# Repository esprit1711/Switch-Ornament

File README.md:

# Switch-Ornament
tinyest possible Gif Player that looks like a Nintendo Switch
IN CASE YOU WANT TO BUILD YOUR OWN SWITCH ORNAMENT, PLEASE CONTACT ME. I WANT TO FIX SOME TINY PROBLEMS WITH THE BOARD IN VERSION 1.4 :)

Here, you will find everything to Copy my GIF Player, that looks like a Nintendo Switch. This Project use a 0.96" 80x160 Pixel TFT with st7735 Driver.
The Source Code is based on the "ESP32-LGFX-SDCard-GifPlayer" Example of the "AnimatedGIF" library from "bitbank2".
The Inspiration for this Project is the Nintendo Switch Ornamend from scottbez1 (you can find his Video in der Credits). He use a slightly bigger Screen, with much higher Resolution but i want the smalest possible Switch.

Part of this Project is a DIY Powerbank only for this device so you can use it as a christmas ornament. Powerbank and Switch are connected over a 65cm long cable with 0.04mm² wires. to achive also the tinyest possible powerbank, i crated a custom Board with Li-Po Charger and Power Switch (you can charge the battery and can still use the device). To use the powerbank also as base, i put 3 magnets inside the switch case and powerbank so it will hold very well together without any bad looking mechanic

The Mainboard is optimised to be ordered at jlcpcb and use the assembly Service. You will find everything jlcpcb need (gerber, BOM and positions file) in the "production" Folder of the KiCad Project. You want to choose a 1.6mm board thickness, the Option "Specify a location" at "Remove Order Number" and check the orientation of every part after upload and check the BOM. You also need to order the tiny Buttons and the TFT so you can assemble it after you got the Boards.

Buttons:

https://de.aliexpress.com/item/1005003752959323.html

0.96" TFT (WELDET TYPE!):

https://de.aliexpress.com/item/1005003806330978.html

After everything is assembled, you need to prepare a USB Cable so the connection will match with the silkscreen. You can solder it directly on the Pads, or use a 1.27mm pinheader. Solder the "BOOT" bridge at the front of the board, connect the USB cable to your PC, open the Firmware with Arduino IDE and upload the Code.
To upload the code, you need to copy the library folder in your local Arduino library folder and install the ESP32 via Board Manager. after you prepared this, you just need to choose the right board (ESP32C3 Dev Module) and Port and set every setting like on the following picture:

After a successful upload, disconnect the USB cable and remove the "BOOT" solder bridge. Now, you dont need to solder the Bridge anymore to upload a Code via USB. You can also disconnect the USB Cable (or leave it, if you want to use it as the power source) and power the device via the +5V and GND Pads. The Software is prepared to update the firmware, if a "SO_update.bin" was found on the SD-Card, so in case of an Update, you dont need the USB connection anymore.

The Case for the powerbank is printed with an FDM 3D Printer. You need 3x M2 Threaded inserts and M2x6mm screws to assemble everything. As a battery, i use 402535 320mAh LiPo. A piece of double sieded tape between the battery and board is recommended.

The magnets i use are 2mm x 1mm (diameter x thickness). Use a pen to mark the polarity, so you know everytime the orientation.

The Case for the Nintendo Switch is printed with an Resin Printer. I had to do some tests to find the perfect dimensions, but now everything should fit very well.
Paint can bring some thickness, so be carefull with to mouch Paint.

Hardware:

Changelog:
1.1:
- Support for alternative ST7735 Displays (if Color ist wrong, try GPIO09 connect to VCC (alternative Display Type))

1.2:
- Check for GIF Header. Ignor file if Header ist not "GIF"
- alternative library (chose before compile code)

1.3:
- PNG support
- Left Button trigger play previous file instead of changing the Brightness of the Screen

1.4:
- Clean Code, so it should be now better to maintain
- Fix a problem when use the LGFX library (use a variable from eSPI to initialise the SD Card (old testing stuff))
- improve Version Information and SD Card Info Screen. Its now cleaner and stay for 2 instead of 1 second
- change brightness level by push and hold left (reduce) or right (increase) button for more than 1 second
- speed up initialisation slightly

Credits:

https://github.com/bitbank2/AnimatedGIF

https://github.com/Bodmer/TFT_eSPI

https://www.youtube.com/watch?v=zJxyTgLjIB8

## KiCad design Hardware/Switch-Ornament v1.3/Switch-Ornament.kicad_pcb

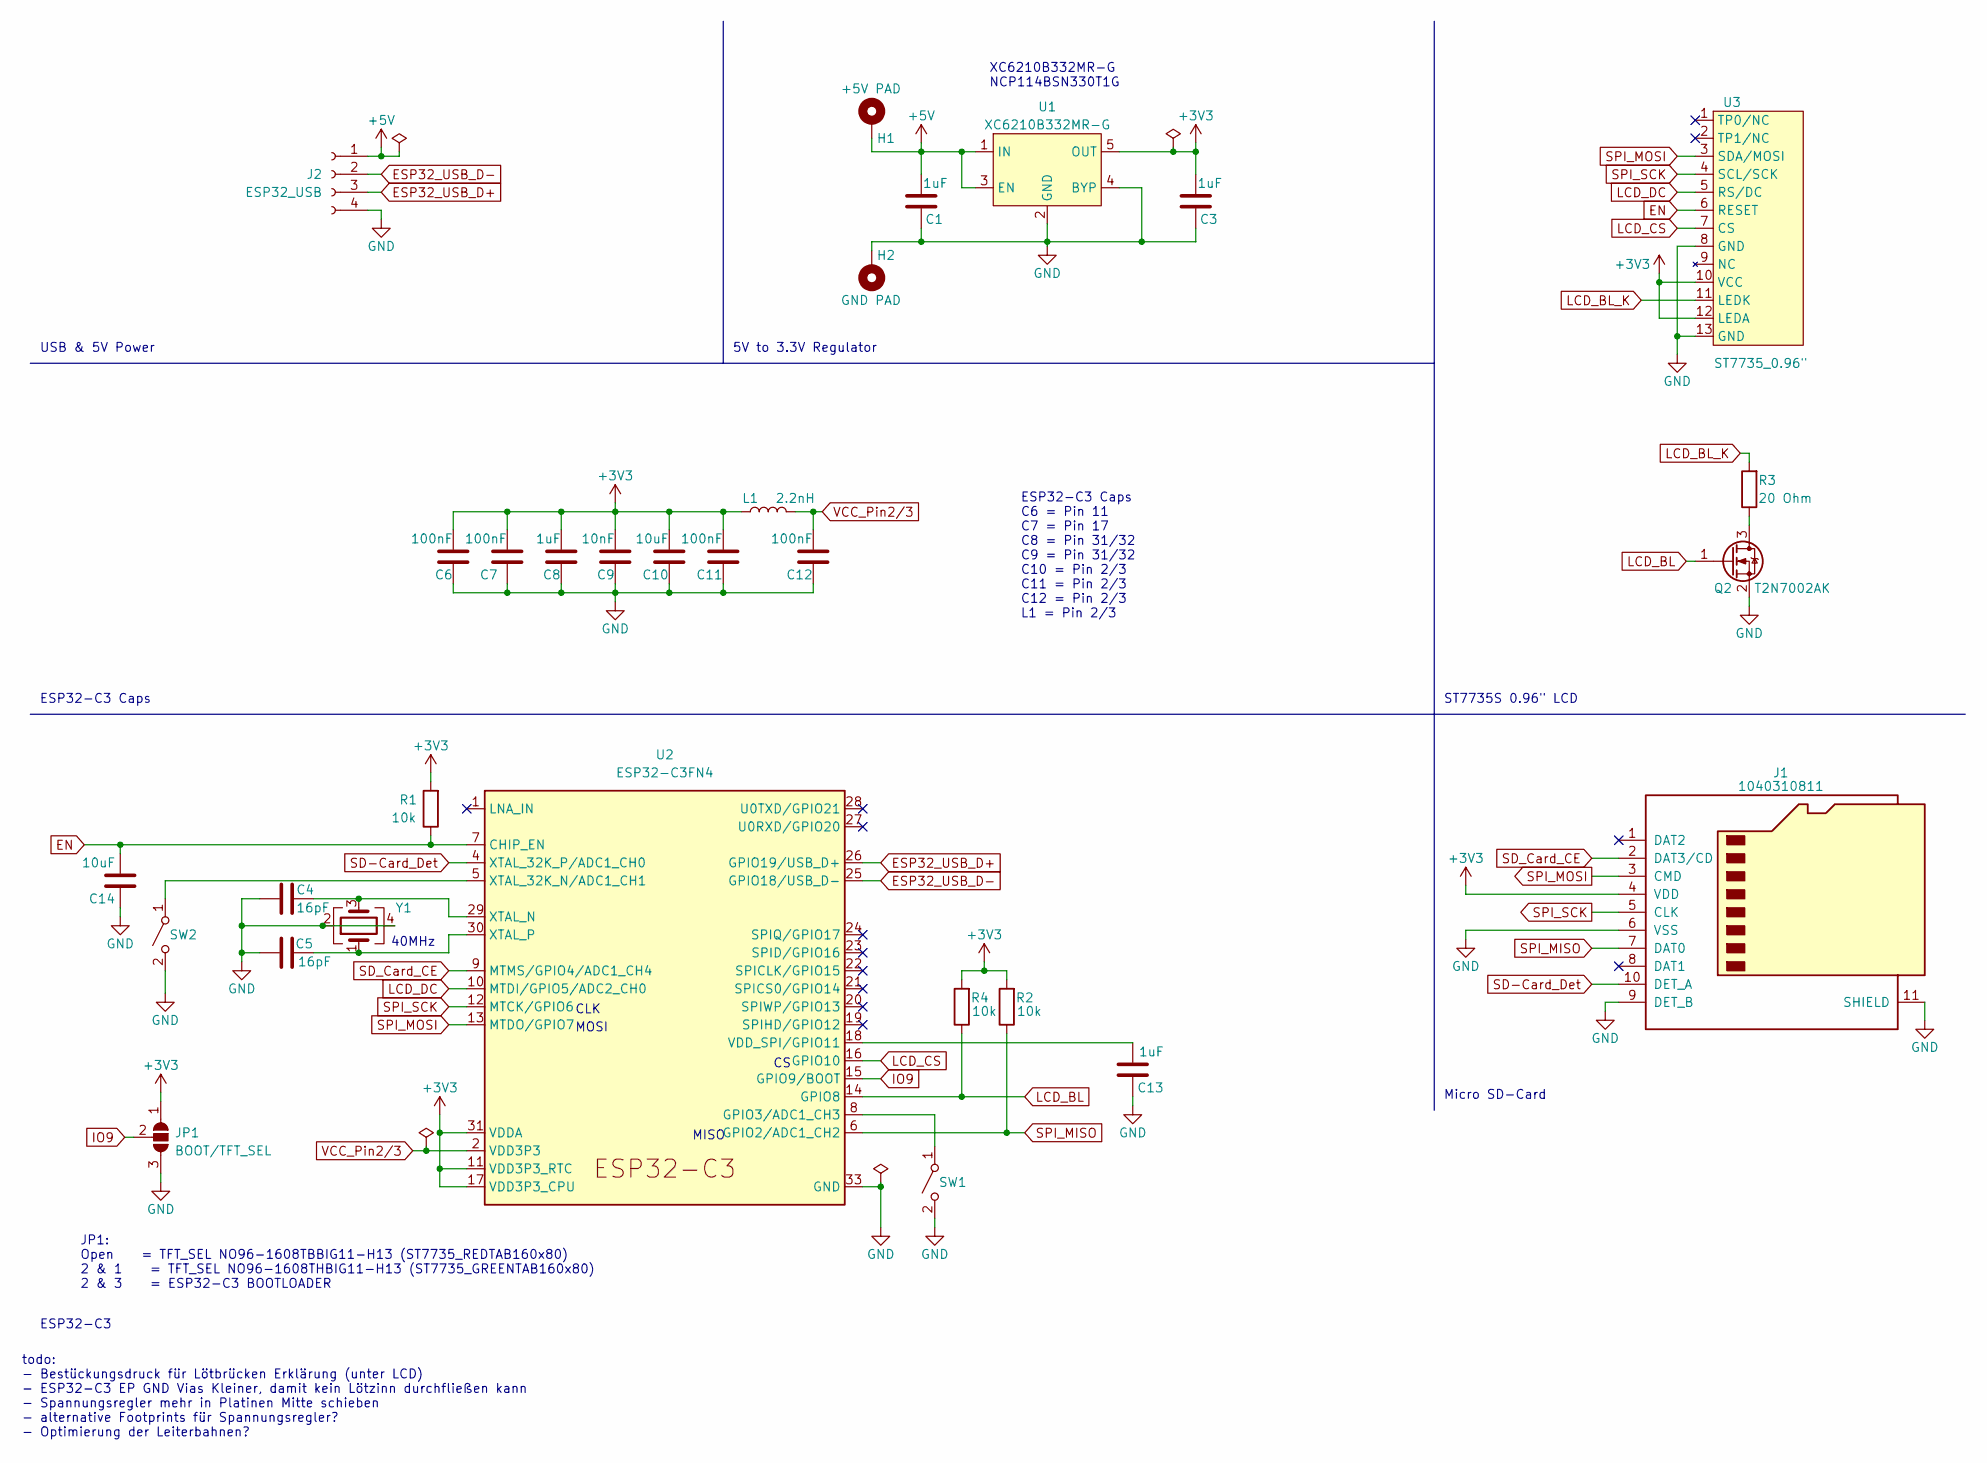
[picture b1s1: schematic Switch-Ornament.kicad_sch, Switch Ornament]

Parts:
C1, C3, C8, C13: 1uF; C_0603_1608Metric
C4, C5: 16pF; C_0603_1608Metric
C6, C7, C11, C12: 100nF; C_0603_1608Metric
C9: 10nF; C_0603_1608Metric
C10, C14: 10uF; C_0603_1608Metric
H1: +5V PAD; TestPoint_Pad_D1.5mm
H2: GND PAD; TestPoint_Pad_D1.5mm
J1: 1040310811; microSD_HC_Molex_104031-0811
J2: ESP32_USB; PinHeader_1x04_P1.27mm_Vertical
JP1: BOOT/TFT_SEL; SolderJumper-3_P2.0mm_Open_TrianglePad1.0x1.5mm_NumberLabels
L1: 2.2nH; L_0603_1608Metric
Q2: T2N7002AK; SOT-23
R1, R2, R4: 10k; R_0603_1608Metric
R3: 20 Ohm; R_0603_1608Metric
SW1, SW2: EVP-BB2A9B000; EVPBB
U1: XC6210B332MR-G; TSOP-5_1.65x3.05mm_P0.95mm
U2: ESP32-C3FN4; QFN-32-1EP_5x5mm_P0.5mm_EP3.45x3.45mm
U3: ST7735_0.96"; ST7735S 0.96
Y1: 7B040000H01; Crystal_SMD_3225-4Pin_3.2x2.5mm

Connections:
+3V3: C3.2, C6.2, C7.2, C8.2, C9.2, C10.2, C11.2, J1.4 (VDD), JP1.1 (A), L1.1, R1.2, R2.2, R4.2, U1.5 (OUT), U2.11 (VDD3P3_RTC), U2.17 (VDD3P3_CPU), U2.31 (VDDA), U2.32 (VDDA), U3.10 (VCC), U3.12 (LEDA)
+5V: C1.2, H1.1, J2.1, U1.1 (IN), U1.3 (EN)
EN: C14.2, R1.1, U2.7 (CHIP_EN), U3.6 (RESET)
ESP32_USB_D+: J2.3, U2.26 (GPIO19/USB_D+)
ESP32_USB_D-: J2.2, U2.25 (GPIO18/USB_D-)
GND: C1.1, C3.1, C4.2, C5.1, C6.1, C7.1, C8.1, C9.1, C10.1, C11.1, C12.1, C13.1, C14.1, H2.1, J1.6 (VSS), J1.9 (DET_B), J1.11 (SHIELD), J2.4, JP1.3 (B), Q2.2 (S), SW1.2 (B), SW2.2 (B), U1.2 (GND), U1.4 (BYP), U2.33 (GND), U3.8 (GND), U3.13 (GND), Y1.2, Y1.4
IO9: JP1.2 (C), U2.15 (GPIO9/BOOT)
LCD_BL: Q2.1 (G), R4.1, U2.14 (GPIO8)
LCD_BL_K: R3.2, U3.11 (LEDK)
LCD_CS: U2.16 (GPIO10), U3.7 (CS)
LCD_DC: U2.10 (MTDI/GPIO5/ADC2_CH0), U3.5 (RS/DC)
unnamed: Q2.3 (D), R3.1
unnamed: SW1.1 (A), U2.8 (GPIO3/ADC1_CH3)
unnamed: SW2.1 (A), U2.5 (XTAL_32K_N/ADC1_CH1)
unnamed: C13.2, U2.18 (VDD_SPI/GPIO11)
unnamed: C4.1, U2.29 (XTAL_N), Y1.3
unnamed: C5.2, U2.30 (XTAL_P), Y1.1
SD-Card_Det: J1.10 (DET_A), U2.4 (XTAL_32K_P/ADC1_CH0)
SD_Card_CE: J1.2 (DAT3/CD), U2.9 (MTMS/GPIO4/ADC1_CH4)
SPI_MISO: J1.7 (DAT0), R2.1, U2.6 (GPIO2/ADC1_CH2)
SPI_MOSI: J1.3 (CMD), U2.13 (MTDO/GPIO7), U3.3 (SDA/MOSI)
SPI_SCK: J1.5 (CLK), U2.12 (MTCK/GPIO6), U3.4 (SCL/SCK)
VCC_Pin2/3: C12.2, L1.2, U2.2 (VDD3P3), U2.3 (VDD3P3)

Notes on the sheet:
ST7735S 0.96" LCD
CLK
40MHz
USB & 5V Power
XC6210B332MR-G NCP114BSN330T1G
ESP32-C3 Caps
MOSI
Micro SD-Card
todo: - Bestückungsdruck für Lötbrücken Erklärung (unter LCD) - ESP32-C3 EP GND Vias Kleiner, damit kein Lötzinn durchfließen kann - Spannungsregler mehr in Platinen Mitte schieben - alternative Footprints für Spannungsregler? - Optimierung der Leiterbahnen?
ESP32-C3 Caps C6 = Pin 11 C7 = Pin 17 C8 = Pin 31/32 C9 = Pin 31/32 C10 = Pin 2/3 C11 = Pin 2/3 C12 = Pin 2/3 L1 = Pin 2/3
MISO
ESP32-C3
JP1: Open = TFT_SEL NO96-1608TBBIG11-H13 (ST7735_REDTAB160x80) 2 & 1 = TFT_SEL NO96-1608THBIG11-H13 (ST7735_GREENTAB160x80) 2 & 3 = ESP32-C3 BOOTLOADER
5V to 3.3V Regulator

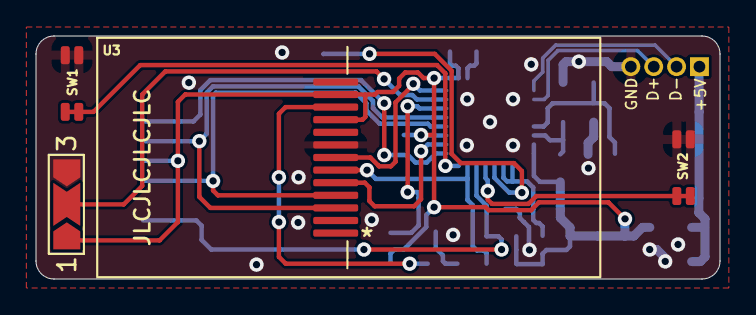
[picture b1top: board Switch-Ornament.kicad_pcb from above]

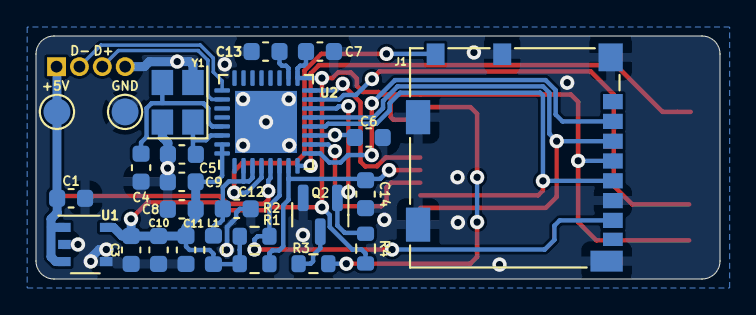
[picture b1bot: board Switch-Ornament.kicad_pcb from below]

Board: 2 copper layers, 38.0 x 13.5 mm, 30 parts (26 on the bottom side), 23 nets.

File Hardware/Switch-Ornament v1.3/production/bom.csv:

Designator,Footprint,Quantity,Value,LCSC Part #
"C1, C13, C3, C8",0603,4,1uF,
"C10, C14",0603,2,10uF,
"C11, C12, C6, C7",0603,4,100nF,
"C4, C5",0603,2,16pF,
C9,0603,1,10nF,
H1,TestPoint_Pad_D1.5mm,1,+5V PAD,
H2,TestPoint_Pad_D1.5mm,1,GND PAD,
J1,microSD_HC_Molex_104031-0811,1,1040310811,
J2,PinHeader_1x04_P1.27mm_Vertical,1,ESP32_USB,
JP1,SolderJumper-2_P1.3mm_Open_TrianglePad1.0x1.5mm,1,BOOT,
L1,0603,1,2.2nH,
Q2,SOT-23,1,T2N7002AK,
"R1, R2, R4",0603,3,10k,
R3,0603,1,20 Ohm,
"SW1, SW2",EVPBB,2,EVP-BB2A9B000,
U1,TSOP-5_1.65x3.05mm_P0.95mm,1,XC6210B332MR-G,
U2,QFN-32-1EP_5x5mm_P0.5mm_EP3.45x3.45mm,1,ESP32-C3FN4,
U3,ST7735S 0.96,1,"ST7735_0.96""",
Y1,Crystal_SMD_3225-4Pin_3.2x2.5mm,1,7B040000H01,

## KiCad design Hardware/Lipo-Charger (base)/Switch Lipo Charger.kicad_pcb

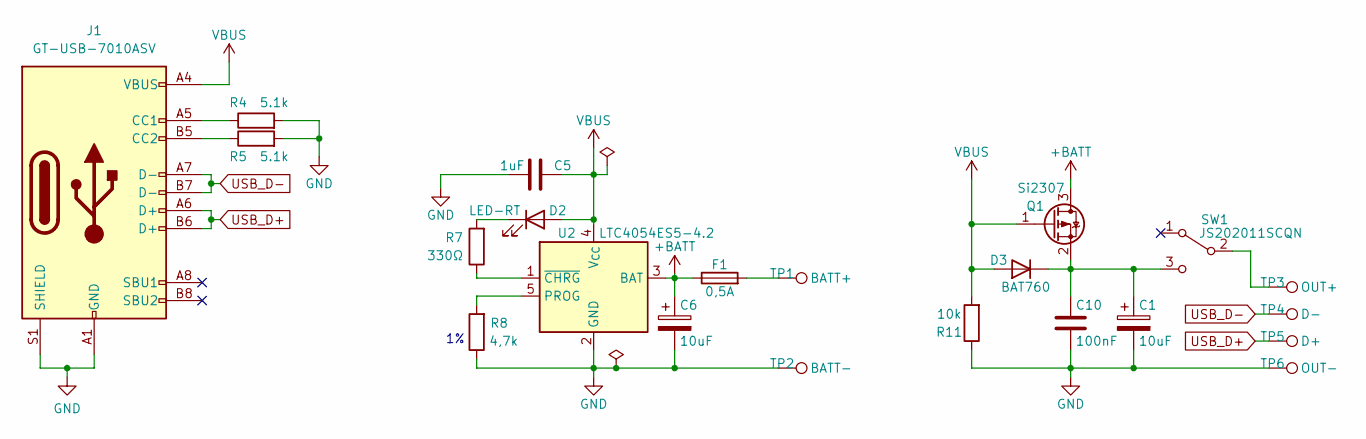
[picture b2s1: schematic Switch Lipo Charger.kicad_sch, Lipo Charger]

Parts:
C1, C6: 10uF; CP_EIA-2012-15_AVX-P_Pad1.30x1.05mm_HandSolder
C5: 1uF; C_0805_2012Metric_Pad1.18x1.45mm_HandSolder
C10: 100nF; C_0603_1608Metric_Pad1.08x0.95mm_HandSolder
D2: LED-RT; LED_0805_2012Metric_Pad1.15x1.40mm_HandSolder
D3: BAT760; D_SOD-123F
F1: 0,5A; Fuse_1206_3216Metric_Pad1.42x1.75mm_HandSolder
J1: GT-USB-7010ASV; USB_C_Receptacle_G-Switch_GT-USB-7010ASV
Q1: Si2307; SOT-23
R4, R5: 5.1k; R_0603_1608Metric_Pad0.98x0.95mm_HandSolder
R7: 330Ω; R_0603_1608Metric_Pad0.98x0.95mm_HandSolder
R8: 4,7k; R_0603_1608Metric_Pad0.98x0.95mm_HandSolder
R11: 10k; R_0603_1608Metric_Pad0.98x0.95mm_HandSolder
SW1: JS202011SCQN
TP1: BATT+; TestPoint_Pad_D2.5mm
TP2: BATT-; TestPoint_Pad_D2.5mm
TP3: OUT+; TestPoint_Pad_D2.0mm
TP4: D-; TestPoint_Pad_D2.0mm
TP5: D+; TestPoint_Pad_D2.0mm
TP6: OUT-; TestPoint_Pad_D2.0mm
U2: LTC4054ES5-4.2; TSOT-23-5

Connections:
+BATT: C6.1, F1.1, Q1.3 (D), U2.3 (BAT)
GND: C1.2, C5.2, C6.2, C10.2, J1.A1 (GND), J1.A12 (GND), J1.B1 (GND), J1.B12 (GND), J1.S1 (SHIELD), R4.2, R5.2, R8.1, R11.1, TP2.1, TP6.1, U2.2 (GND)
unnamed: D2.1 (K), R7.2
unnamed: C1.1, C10.1, D3.1 (K), Q1.2 (S), SW1.3 (C)
unnamed: F1.2, TP1.1
unnamed: J1.A5 (CC1), R4.1
unnamed: J1.B5 (CC2), R5.1
unnamed: SW1.2 (B), TP3.1
unnamed: R8.2, U2.5 (PROG)
unnamed: R7.1, U2.1 (~CHRG)
USB_D+: J1.A6 (D+), J1.B6 (D+), TP5.1
USB_D-: J1.A7 (D-), J1.B7 (D-), TP4.1
VBUS: C5.1, D2.2 (A), D3.2 (A), J1.A4 (VBUS), J1.A9 (VBUS), J1.B4 (VBUS), J1.B9 (VBUS), Q1.1 (G), R11.2, U2.4 (V_{CC})

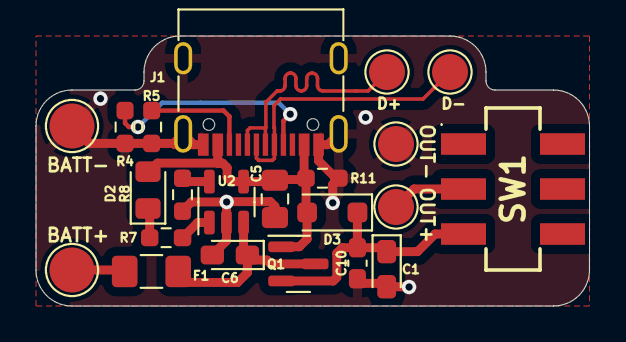
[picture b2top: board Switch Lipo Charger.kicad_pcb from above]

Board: 2 copper layers, 30.8 x 15.0 mm, 22 parts (0 on the bottom side), 13 nets.

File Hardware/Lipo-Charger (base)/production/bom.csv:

Designator,Footprint,Quantity,Value,LCSC Part #
"C1, C6",CP_EIA-2012-15_AVX-P_Pad1.30x1.05mm_HandSolder,2,10uF,
C10,0603,1,100nF,
C5,0805,1,1uF,
D2,0805,1,LED-RT,
D3,D_SOD-123F,1,BAT760,
F1,1206,1,"0,5A",
J1,USB_C_Receptacle_G-Switch_GT-USB-7010ASV,1,GT-USB-7010ASV,
Q1,SOT-23,1,Si2307,
R11,0603,1,10k,
"R4, R5",0603,2,5.1k,
R7,0603,1,330Ω,
R8,0603,1,"4,7k",
SW1,JS202011SCQN,1,JS202011SCQN,
TP1,TestPoint_Pad_D2.5mm,1,BATT+,
TP2,TestPoint_Pad_D2.5mm,1,BATT-,
TP3,TestPoint_Pad_D2.0mm,1,OUT+,
TP4,TestPoint_Pad_D2.0mm,1,D-,
TP5,TestPoint_Pad_D2.0mm,1,D+,
TP6,TestPoint_Pad_D2.0mm,1,OUT-,
U2,TSOT-23-5,1,LTC4054ES5-4.2,

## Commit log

2023-04-07 Initial Release
2023-09-02 v1.4 release
    Release of Version 1.4:
    Changelog:
    1.1:
    - Support for alternative ST7735 Displays (if Color ist wrong, try GPIO09 connect to VCC (alternative Display Type))
    1.2:
    - Check for GIF Header. Ignor file if Header ist not "GIF"
2023-09-02 Update Mechanic and Hardware
2023-09-02 add Changelog
2023-09-02 in case of recreate Switch Ornament - Info
